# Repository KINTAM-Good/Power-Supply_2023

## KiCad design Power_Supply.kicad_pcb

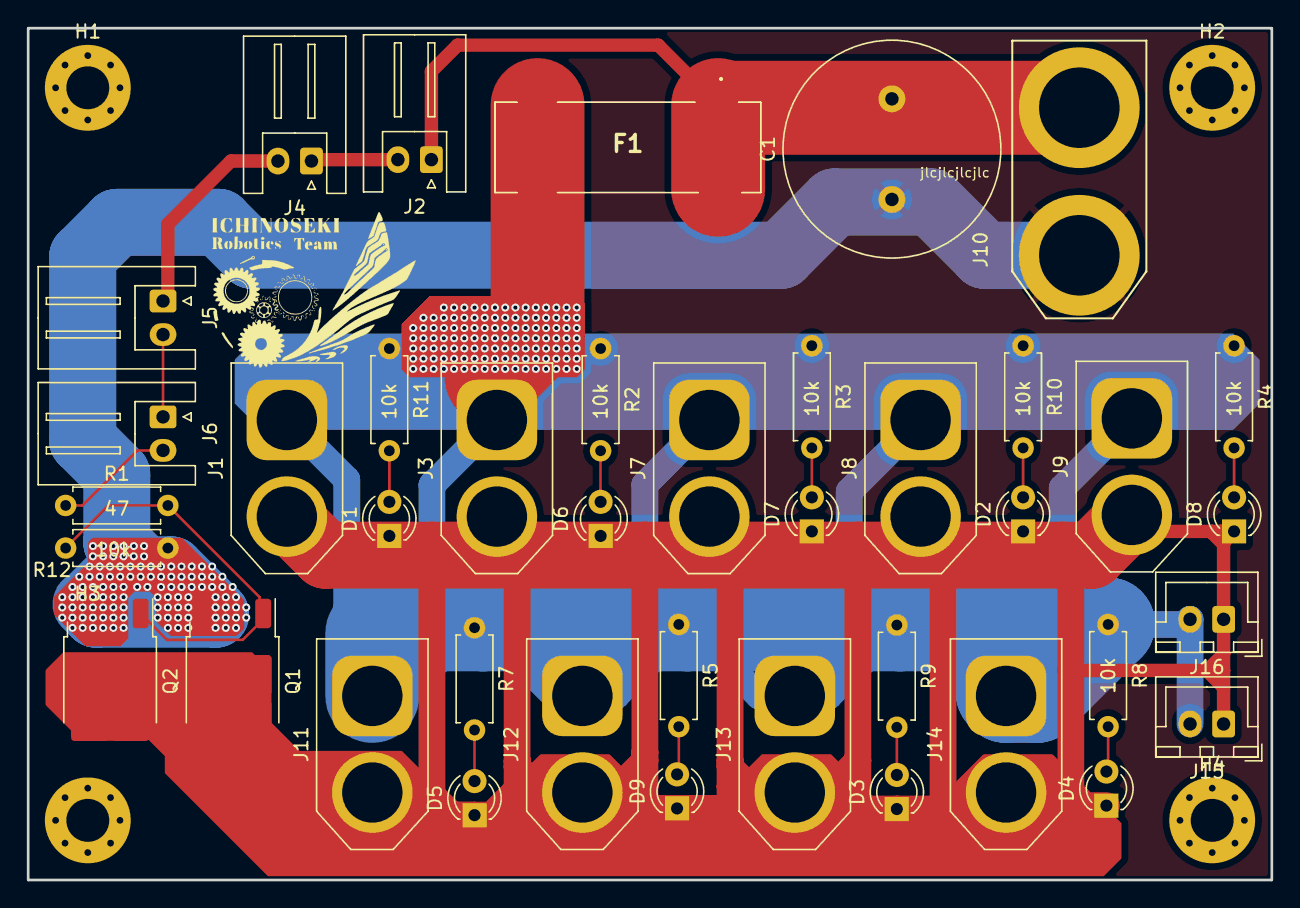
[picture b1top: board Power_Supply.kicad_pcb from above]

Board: 2 copper layers, 92.7 x 63.5 mm, 45 parts (0 on the bottom side), 18 nets.

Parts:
C1: C; C_Radial_D16.0mm_H25.0mm_P7.50mm
D1, D2, D3, D4, D5, D6, D7, D8, D9: LED; LED_D3.0mm
F1: Fuse; 358720
H1, H2, H3, H4: MountingHole; MountingHole_3.2mm_M3_Pad_Via
J1, J3, J7, J8, J9, J11, J12, J13, J14: Conn_01x02_Female; AMASS_XT60-F_1x02_P7.20mm_Vertical
J2, J4, J5, J6: Conn_01x02_Female; JST_XH_S2B-XH-A_1x02_P2.50mm_Horizontal
J8#2: Logo; INCT
J10: Conn_01x02_Male; XT90
J15, J16: Conn_01x02_Female; JST_XH_B2B-XH-A_1x02_P2.50mm_Vertical
Q1, Q2: Q_NMOS_GDSD; TO-252-2
R1: 47; R_Axial_DIN0207_L6.3mm_D2.5mm_P7.62mm_Horizontal
R2, R3, R4, R5, R7, R8, R9, R10, R11, R12: 10k; R_Axial_DIN0207_L6.3mm_D2.5mm_P7.62mm_Horizontal

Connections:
+18V: C1.2, F1.1, J2.1, J10.1
GND: C1.1, J10.2, Q1.3 (S), Q2.3 (S), R12.2
Moter_IN: F1.2, J1.2, J3.2, J7.2, J8.2, J9.2, J11.2, J12.2, J13.2, J14.2, J15.2, J16.2, R2.1, R3.1, R4.1, R5.1, R7.1, R8.1, R9.1, R10.1, R11.1
Moter_OUT: D1.1 (K), D2.1 (K), D3.1 (K), D4.1 (K), D5.1 (K), D6.1 (K), D7.1 (K), D8.1 (K), D9.1 (K), J1.1, J3.1, J7.1, J8.1, J9.1, J11.1, J12.1, J13.1, J14.1, J15.1, J16.1, Q1.2 (D), Q2.2 (D)
unnamed: D1.2 (A), R11.2
unnamed: D2.2 (A), R10.2
unnamed: D3.2 (A), R9.2
unnamed: D4.2 (A), R8.2
unnamed: D5.2 (A), R7.2
unnamed: D6.2 (A), R2.2
unnamed: D7.2 (A), R3.2
unnamed: D8.2 (A), R4.2
unnamed: D9.2 (A), R5.2
unnamed: J2.2, J4.1
unnamed: J4.2, J5.1
unnamed: J5.2, J6.1
unnamed: J6.2, R1.1
unnamed: Q1.1 (G), Q2.1 (G), R1.2, R12.1
